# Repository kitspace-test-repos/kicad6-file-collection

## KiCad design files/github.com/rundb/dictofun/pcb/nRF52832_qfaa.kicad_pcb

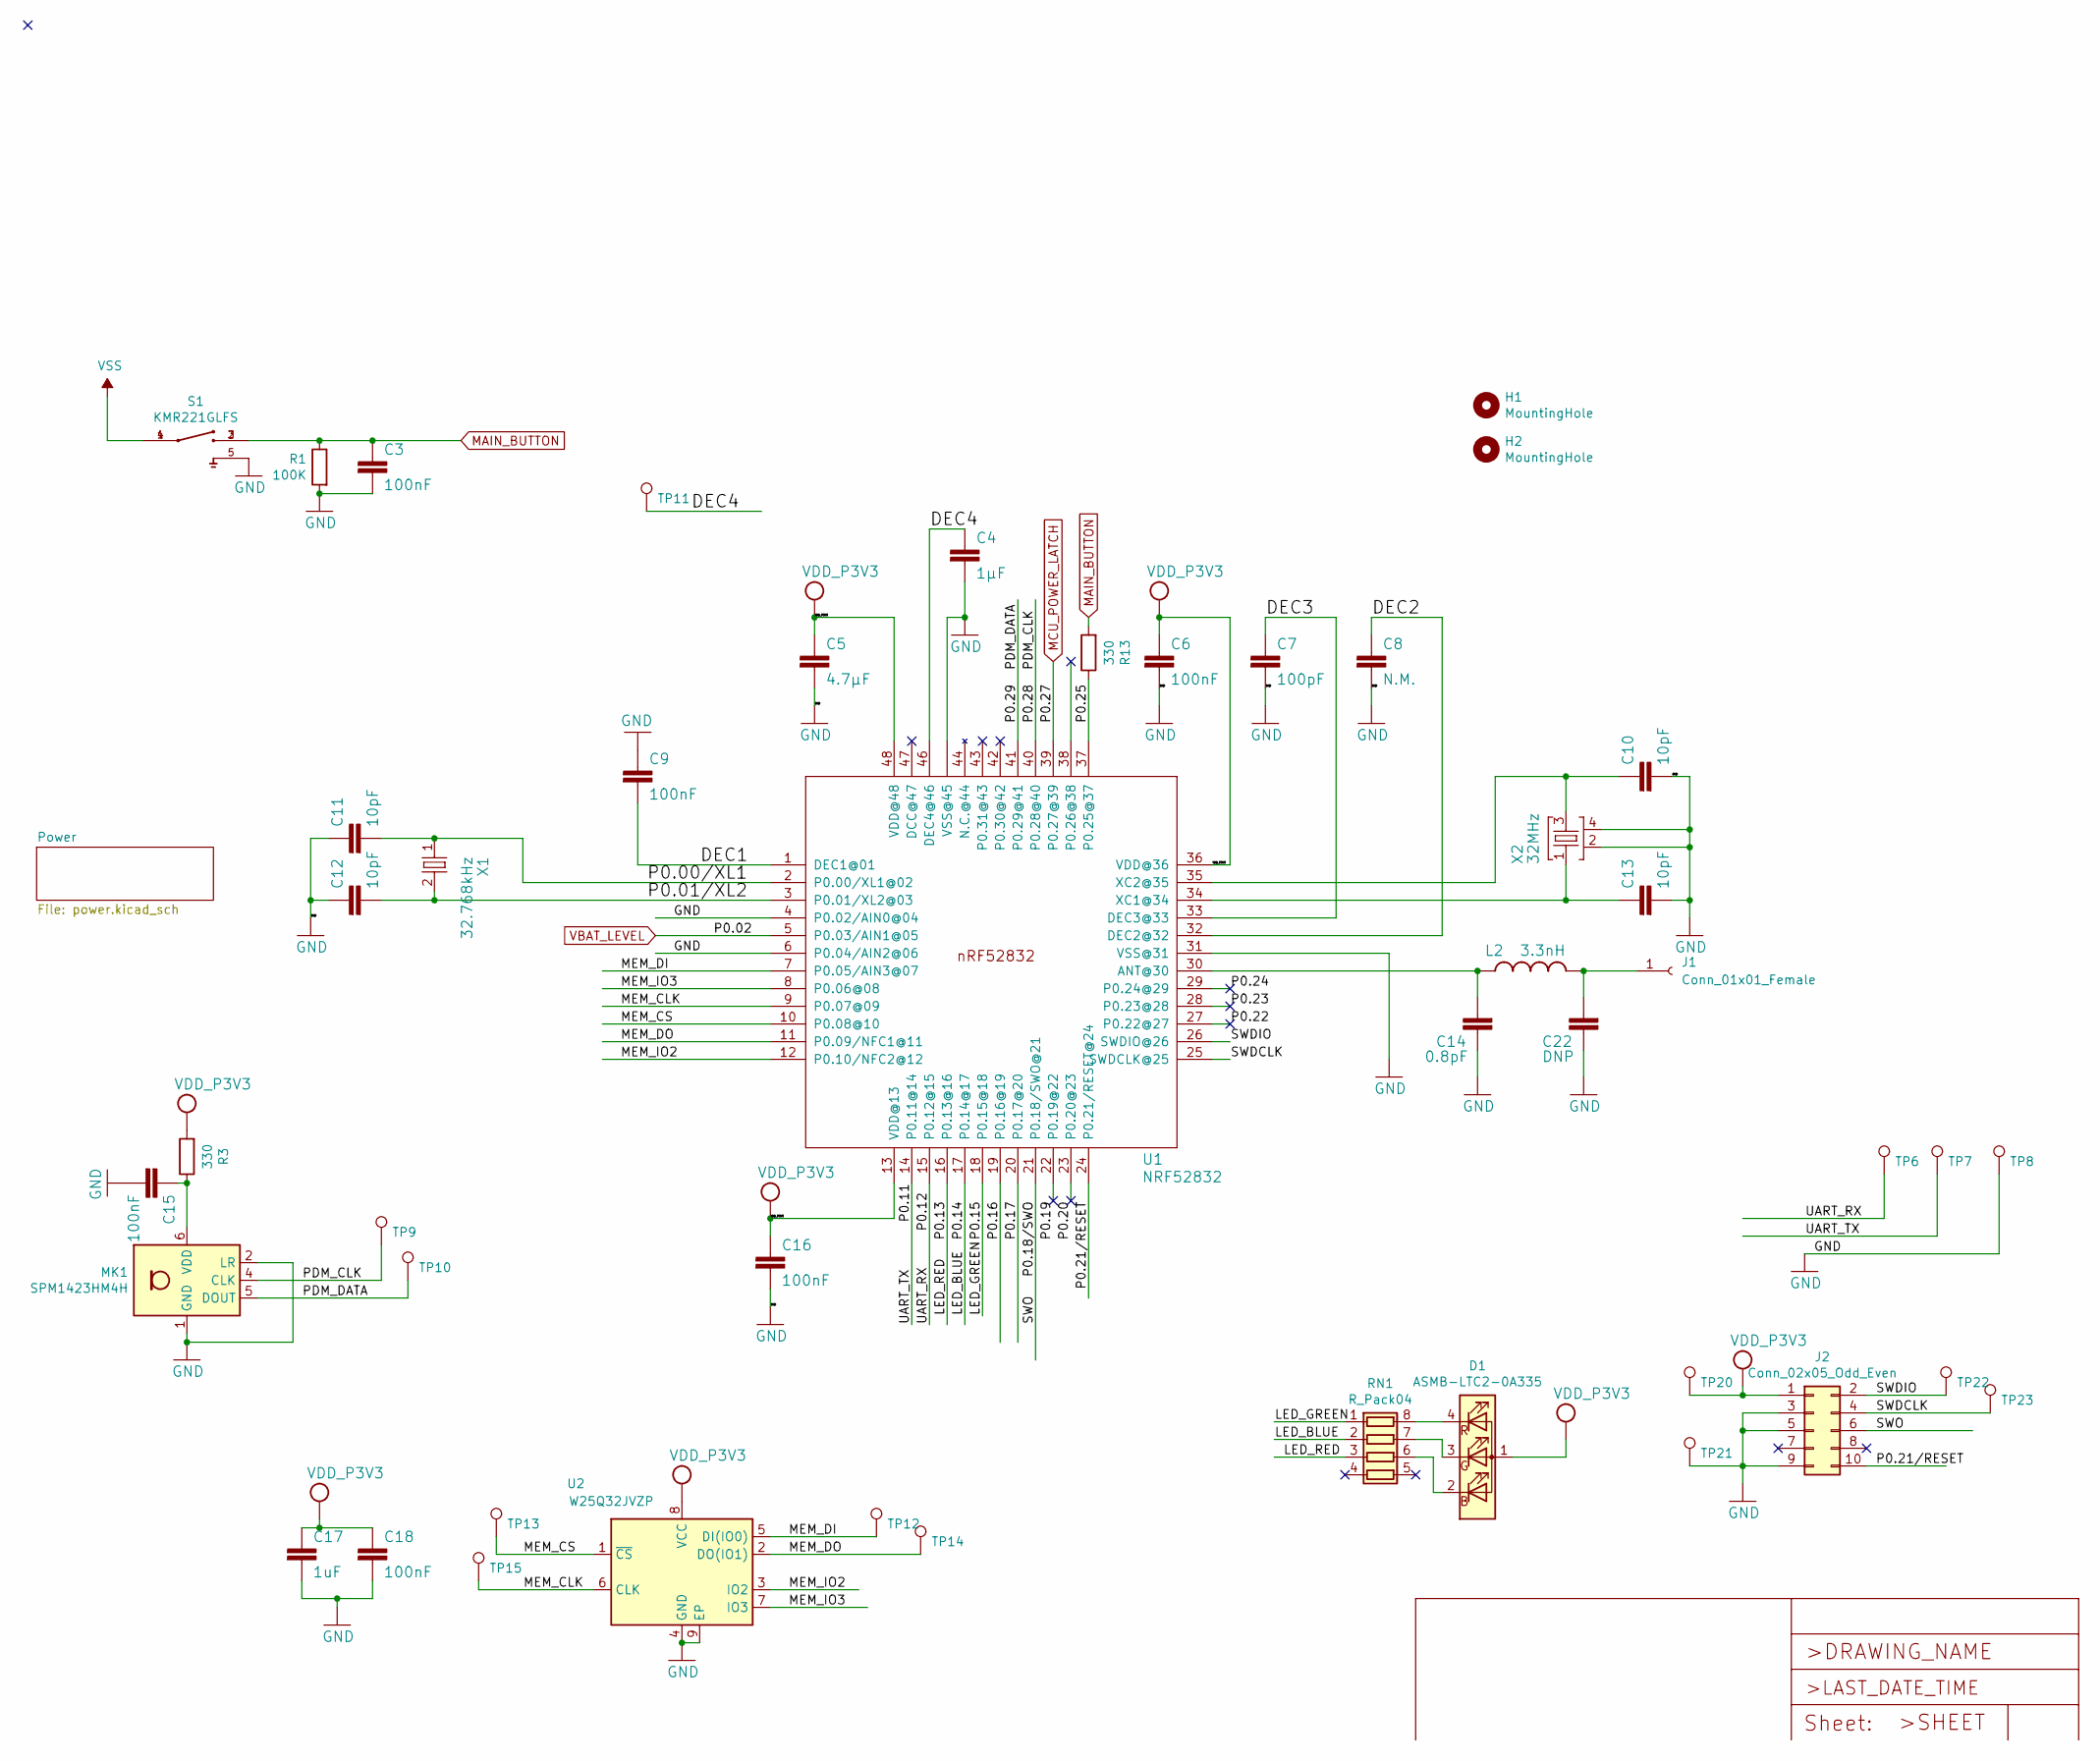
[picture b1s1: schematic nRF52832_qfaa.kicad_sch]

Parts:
C3, C6, C9, C15, C16, C18: 100nF; C_0402_1005Metric; LCSC C1525
C4: 1µF; C_0402_1005Metric; LCSC C92755
C5: 4.7µF; C_0402_1005Metric; LCSC C77004
C7: 100pF; C_0402_1005Metric; LCSC C1546
C8: N.M.; C_0402_1005Metric
C10, C11, C12, C13: 10pF; C_0402_1005Metric; LCSC C32949
C14: 0.8pF; C_0402_1005Metric; LCSC C326068
C17: 1uF; C_0402_1005Metric; LCSC C52923
C22: DNP; C_0402_1005Metric; LCSC C88902
D1: ASMB-LTC2-0A335; LED_Cree-PLCC4_2x2mm_CW
H1, H2: MountingHole; MountingHole_1mm
J1: Conn_01x01_Female; PinHeader_1x01_P1.00mm_Vertical
J2: Conn_02x05_Odd_Even; PinHeader_2x05_P1.27mm_Vertical_SMD
L2: 3.3nH; C_0402_1005Metric; LCSC C162542
MK1: SPM1423HM4H; ST_HLGA-6_3.76x4.72mm_P1.65mm
R1: 100K; R_0402_1005Metric; LCSC C25741
R3, R13: 330; R_0402_1005Metric; LCSC C25104
RN1: R_Pack04; R_Array_Convex_4x0402; LCSC C25726
S1: KMR221GLFS; SW_KMR221GLFS; LCSC C72443
TP6, TP7, TP8, TP9, TP10, TP11, TP12, TP13, TP14, TP15, TP20, TP21, TP22, TP23: TestPoint; TestPoint_Pad_D1.0mm
U1: NRF52832; QFN40P600X600X90-48_N; LCSC C77540
U2: W25Q32JVZP; WSON-8-1EP_6x5mm_P1.27mm_EP3.4x4.3mm; LCSC C2689660
X1: 32.768kHz; XTAL_3215_N
X2: 32MHz; BT-XTAL_2016_N

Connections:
/DEC1: C9.2, U1.1 (DEC1@01)
/DEC2: C8.1, U1.32 (DEC2@32)
/DEC3: C7.1, U1.33 (DEC3@33)
/DEC4: C4.1, TP11.1, U1.46 (DEC4@46)
/LED_BLUE: RN1.2 (R2.1), U1.17 (P0.14@17)
/LED_GREEN: RN1.1 (R1.1), U1.18 (P0.15@18)
/LED_RED: RN1.3 (R3.1), U1.16 (P0.13@16)
/MEM_CLK: TP15.1, U1.9 (P0.07@09), U2.6 (CLK)
/MEM_CS: TP13.1, U1.10 (P0.08@10), U2.1 (~CS)
/MEM_DI: TP12.1, U1.7 (P0.05/AIN3@07), U2.5 (DI(IO0))
/MEM_DO: TP14.1, U1.11 (P0.09/NFC1@11), U2.2 (DO(IO1))
/MEM_IO2: U1.12 (P0.10/NFC2@12), U2.3 (IO2)
/MEM_IO3: U1.8 (P0.06@08), U2.7 (IO3)
/P0.00/XL1: C11.2, U1.2 (P0.00/XL1@02), X1.1
/P0.01/XL2: C12.2, U1.3 (P0.01/XL2@03), X1.2
/P0.11: TP7.1, U1.14 (P0.11@14)
/P0.12: TP6.1, U1.15 (P0.12@15)
/P0.16: U1.19 (P0.16@19)
/P0.17: U1.20 (P0.17@20)
/P0.18/SWO: J2.6, U1.21 (P0.18/SWO@21)
/P0.19: U1.22 (P0.19@22)
/P0.20: U1.23 (P0.20@23)
/P0.21/RESET: J2.10, U1.24 (P0.21/RESET@24)
/P0.22: U1.27 (P0.22@27)
/P0.23: U1.28 (P0.23@28)
/P0.24: U1.29 (P0.24@29)
/P0.25: R13.1, U1.37 (P0.25@37)
/P0.28: MK1.4 (CLK), TP9.1, U1.40 (P0.28@40)
/P0.29: MK1.5 (DOUT), TP10.1, U1.41 (P0.29@41)
/SWDCLK: J2.4, TP23.1, U1.25 (SWDCLK@25)
/SWDIO: J2.2, TP22.1, U1.26 (SWDIO@26)
GND: C3.2, C4.2, C5.2, C6.2, C7.2, C8.2, C9.1, C10.2, C11.1, C12.1, C13.2, C14.1, C15.2, C16.2, C17.2, C18.2, C22.1, J2.3, J2.5, J2.9, MK1.1 (GND), MK1.2 (LR), MK1.3 (GND), R1.2, S1.5, TP8.1, TP21.1, U1.4 (P0.02/AIN0@04), U1.6 (P0.04/AIN2@06), U1.31 (VSS@31), U1.45 (VSS@45), U1.PAD (VSS@45), U1.PAD@VIA01 (VSS@45), U1.PAD@VIA02 (VSS@45), U1.PAD@VIA03 (VSS@45), U1.PAD@VIA04 (VSS@45), U1.PAD@VIA05 (VSS@45), U1.PAD@VIA06 (VSS@45), U1.PAD@VIA07 (VSS@45), U1.PAD@VIA08 (VSS@45), U1.PAD@VIA09 (VSS@45), U1.PAD@VIA10 (VSS@45), U1.PAD@VIA11 (VSS@45), U1.PAD@VIA12 (VSS@45), U1.PAD@VIA13 (VSS@45), U1.PAD@VIA14 (VSS@45), U1.PAD@VIA15 (VSS@45), U1.PAD@VIA16 (VSS@45), U2.4 (GND), U2.9 (EP), X2.2, X2.4; also elsewhere on the board
MAIN_BUTTON: C3.1, R1.1, R13.2, S1.2, S1.3; also elsewhere on the board
MCU_POWER_LATCH: U1.39 (P0.27@39); also elsewhere on the board
unnamed: C10.1, U1.35 (XC2@35), X2.3
unnamed: C13.1, U1.34 (XC1@34), X2.1
unnamed: C14.2, L2.1, U1.30 (ANT@30)
unnamed: C15.1, MK1.6 (VDD), R3.1
unnamed: C22.2, J1.1, L2.2
unnamed: D1.2 (BK), RN1.6 (R3.2)
unnamed: D1.3 (GK), RN1.7 (R2.2)
unnamed: D1.4 (RK), RN1.8 (R1.2)
VBAT_LEVEL: U1.5 (P0.03/AIN1@05); also elsewhere on the board
VCC: C5.1, C6.1, C16.1, C17.1, C18.1, D1.1 (A), J2.1, R3.2, TP20.1, U1.13 (VDD@13), U1.36 (VDD@36), U1.48 (VDD@48), U2.8 (VCC); also elsewhere on the board
VSS: S1.1, S1.4; also elsewhere on the board

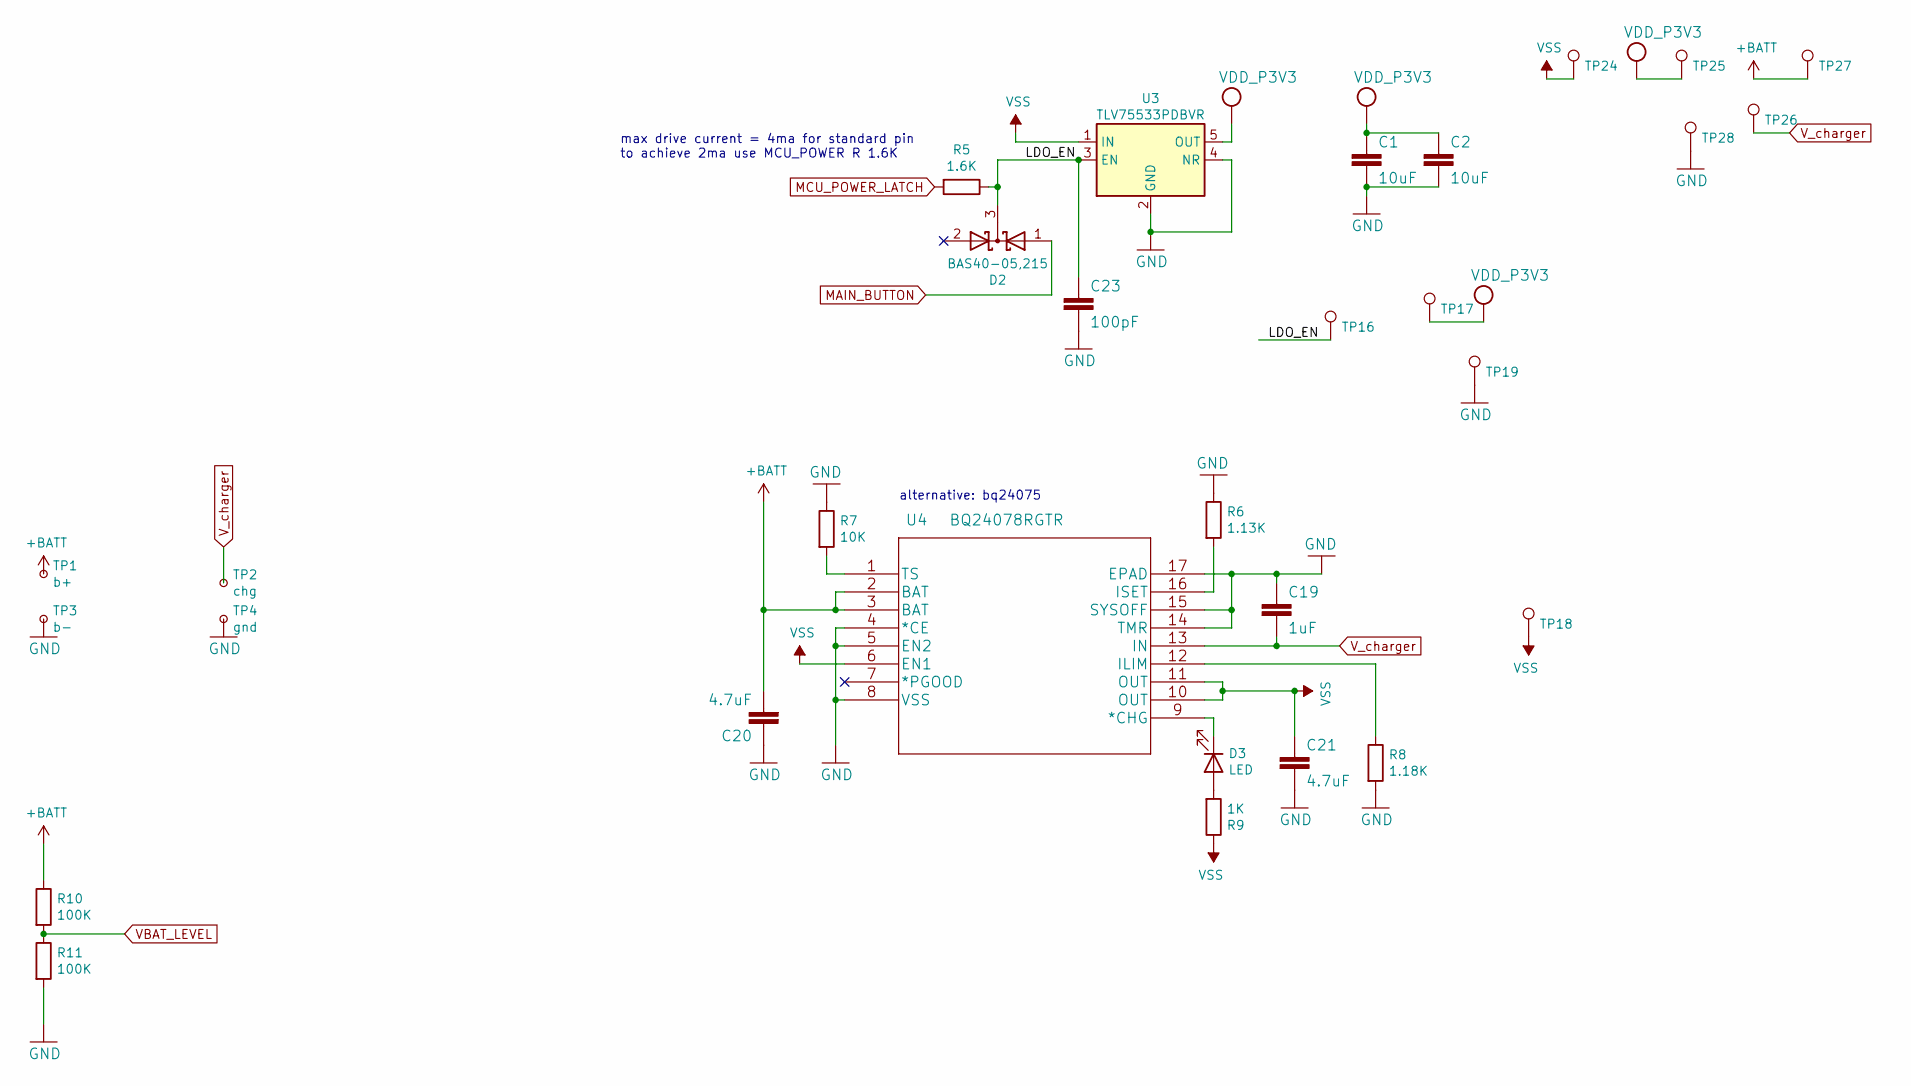
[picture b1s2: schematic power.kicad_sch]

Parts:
C1, C2: 10uF; C_0402_1005Metric; LCSC C15525
C19: 1uF; C_0402_1005Metric; LCSC C52923
C20, C21: 4.7uF; C_0402_1005Metric; LCSC C23733
C23: 100pF; C_0402_1005Metric; LCSC C1546
D2: BAS40-05,215; SOT-23; LCSC C85391
D3: LED; LED_0603_1608Metric; LCSC C72043
R5: 1.6K; R_0402_1005Metric; LCSC C25867
R6: 1.13K; R_0402_1005Metric; LCSC C67014
R7: 10K; R_0402_1005Metric; LCSC C25744
R8: 1.18K; R_0402_1005Metric; LCSC C270651
R9: 1K; R_0402_1005Metric; LCSC C11702
R10, R11: 100K; R_0402_1005Metric; LCSC C25741
TP1: b+; TestPoint_Pad_D1.0mm
TP2: chg; TestPoint_Pad_D1.0mm
TP3: b-; TestPoint_Pad_D1.0mm
TP4: gnd; TestPoint_Pad_D1.0mm
TP16, TP17, TP18, TP19, TP24, TP25, TP26, TP27, TP28: TestPoint; TestPoint_Pad_D1.0mm
U3: TLV75533PDBVR; SOT-23-5; LCSC C404027
U4: BQ24078RGTR; VQFN-16-1EP_3x3mm_P0.5mm_EP1.45x1.45mm_ThermalVias; LCSC C15464

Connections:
+BATT: C20.2, R10.1, TP1.1, TP27.1, U4.2 (BAT), U4.3 (BAT)
/Power/LDO_EN: C23.1, D2.3 (K), R5.1, TP16.1, U3.3 (EN)
GND: C1.2, C2.2, C19.1, C20.1, C21.2, C23.2, R6.1, R7.1, R8.2, R11.2, TP3.1, TP4.1, TP19.1, TP28.1, U3.2 (GND), U3.4 (NR), U4.4 (*CE), U4.5 (EN2), U4.8 (VSS), U4.14 (TMR), U4.15 (SYSOFF), U4.17 (EPAD); also elsewhere on the board
MAIN_BUTTON: D2.1 (A); also elsewhere on the board
MCU_POWER_LATCH: R5.2; also elsewhere on the board
unnamed: D3.1 (K), U4.9 (*CHG)
unnamed: D3.2 (A), R9.2
unnamed: R6.2, U4.16 (ISET)
unnamed: R7.2, U4.1 (TS)
unnamed: R8.1, U4.12 (ILIM)
VBAT_LEVEL: R10.2, R11.1; also elsewhere on the board
VCC: C1.1, C2.1, TP17.1, TP25.1, U3.5 (OUT); also elsewhere on the board
VSS: C21.1, R9.1, TP18.1, TP24.1, U3.1 (IN), U4.6 (EN1), U4.10 (OUT), U4.11 (OUT); also elsewhere on the board
V_charger: C19.2, TP2.1, TP26.1, U4.13 (IN)

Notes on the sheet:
alternative: bq24075
max drive current = 4ma for standard pin to achieve 2ma use MCU_POWER R 1.6K

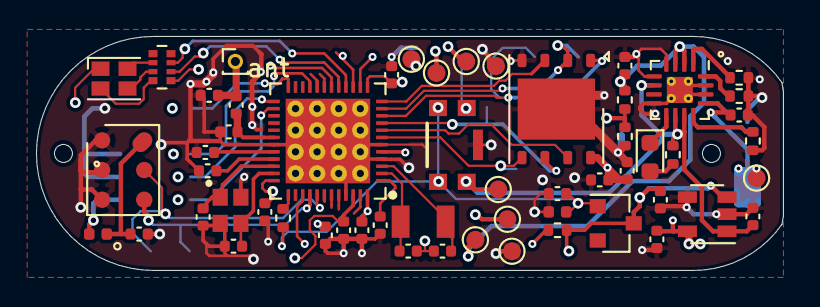
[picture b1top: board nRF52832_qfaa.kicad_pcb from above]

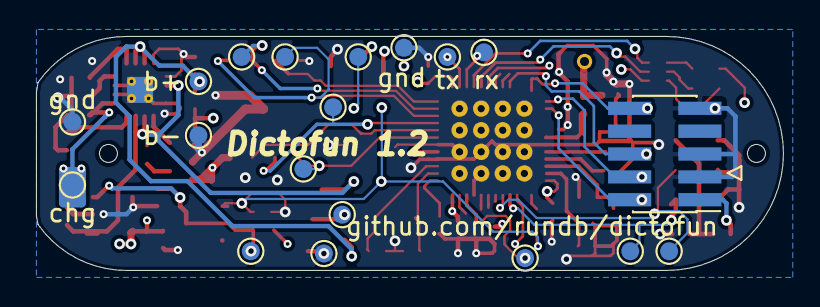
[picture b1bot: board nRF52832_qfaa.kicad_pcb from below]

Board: 4 copper layers, 41.5 x 13.0 mm, 77 parts (19 on the bottom side), 46 nets.

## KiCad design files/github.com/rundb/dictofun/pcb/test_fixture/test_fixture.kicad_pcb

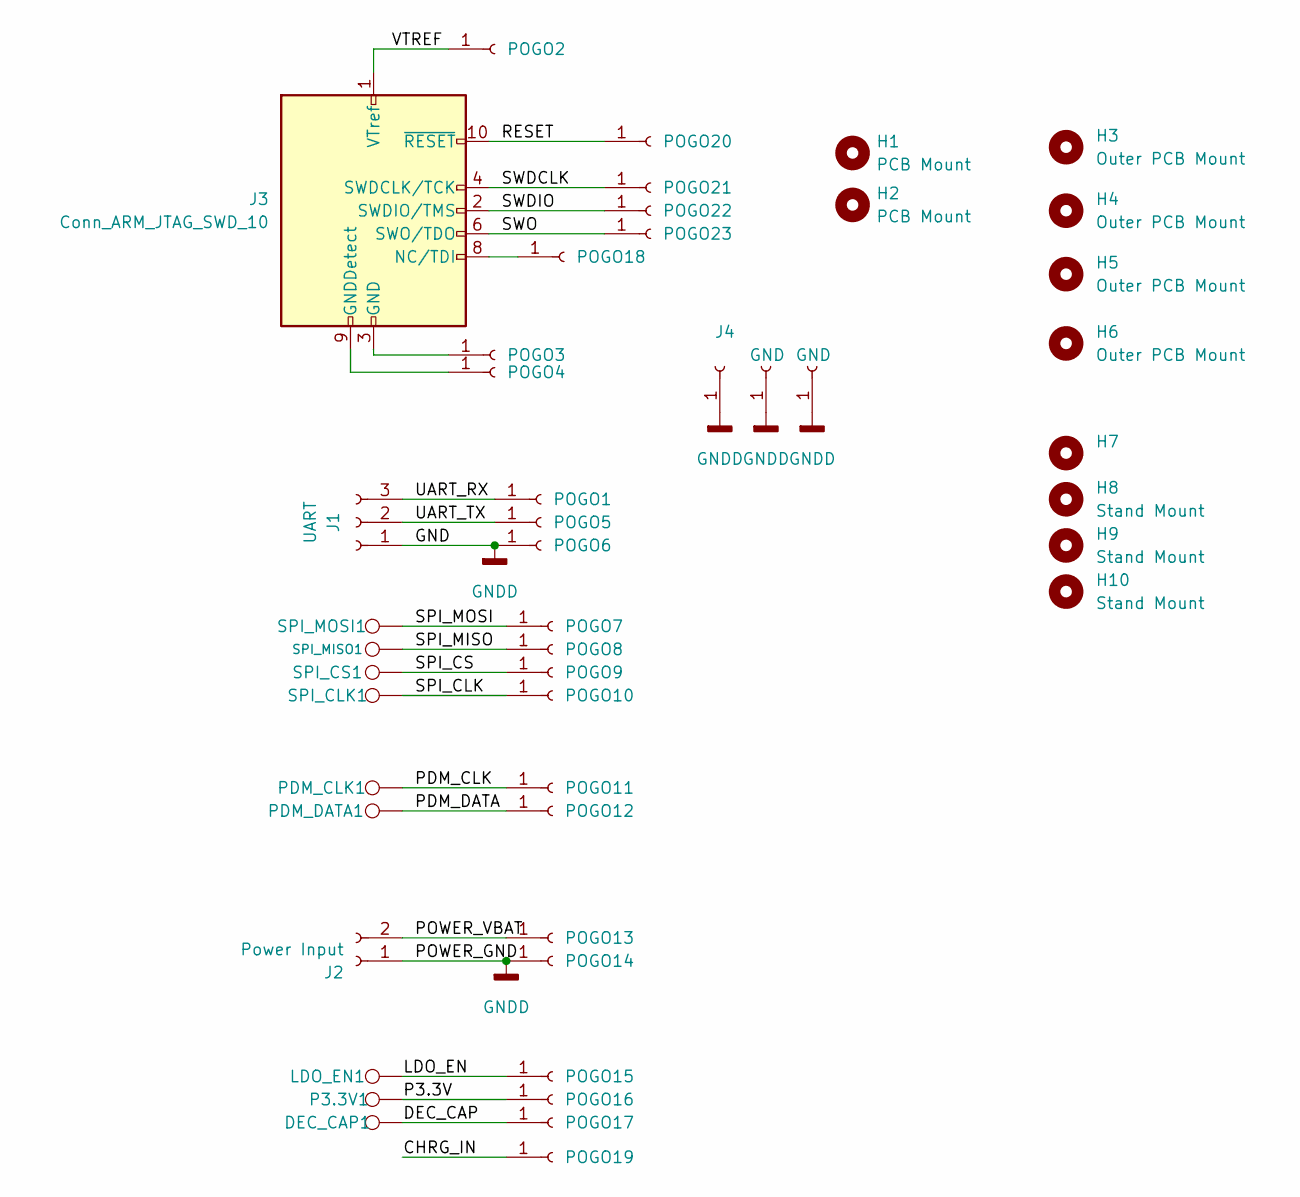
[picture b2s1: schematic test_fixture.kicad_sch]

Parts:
DEC_CAP1: TestPoint_Pad_D1.5mm
H1, H2: PCB Mount; MountingHole_2.1mm
H3, H4, H5, H6: Outer PCB Mount; MountingHole_2.1mm
H7: (no value)
H8, H9, H10: Stand Mount; MountingHole_2.1mm
J1: UART; PinHeader_1x03_P2.54mm_Vertical
J2: Power Input; PinHeader_1x02_P2.54mm_Vertical
J3: Conn_ARM_JTAG_SWD_10; PinHeader_2x05_P1.27mm_Vertical_SMD
J4: PinSocket_1x01_P2.54mm_Vertical
J5, J6: GND; PinSocket_1x01_P2.54mm_Vertical
LDO_EN1: TestPoint_Pad_D1.5mm
P3.3V1: TestPoint_Pad_D1.5mm
PDM_CLK1: TestPoint_Pad_D1.5mm
PDM_DATA1: TestPoint_Pad_D1.5mm
POGO1, POGO2, POGO3, POGO4, POGO5, POGO6, POGO7, POGO8, POGO9, POGO10, POGO11, POGO12, POGO13, POGO14, POGO15, POGO16, POGO17, POGO18, POGO19, POGO20, POGO21, POGO22, POGO23: pogo; POGO_PIN
SPI_CLK1: TestPoint_Pad_D1.5mm
SPI_CS1: TestPoint_Pad_D1.5mm
SPI_MISO1: TestPoint_Pad_D1.5mm
SPI_MOSI1: TestPoint_Pad_D1.5mm

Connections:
/CHRG_IN: POGO19.1
/DEC_CAP: DEC_CAP1.1, POGO17.1
/LDO_EN: LDO_EN1.1, POGO15.1
/P3.3V: P3.3V1.1, POGO16.1
/PDM_CLK: PDM_CLK1.1, POGO11.1
/PDM_DATA: PDM_DATA1.1, POGO12.1
/POWER_VBAT: J2.2, POGO13.1
/RESET: J3.10 (~RESET), POGO20.1
/SPI_CLK: POGO10.1, SPI_CLK1.1
/SPI_CS: POGO9.1, SPI_CS1.1
/SPI_MISO: POGO8.1, SPI_MISO1.1
/SPI_MOSI: POGO7.1, SPI_MOSI1.1
/SWDCLK: J3.4 (SWDCLK/TCK), POGO21.1
/SWDIO: J3.2 (SWDIO/TMS), POGO22.1
/SWO: J3.6 (SWO/TDO), POGO23.1
/UART_RX: J1.3, POGO1.1
/UART_TX: J1.2, POGO5.1
/VTREF: J3.1 (VTref), POGO2.1
GNDD: J1.1, J2.1, J4.1, J5.1, J6.1, POGO6.1, POGO14.1
unnamed: J3.3 (GND), J3.5 (GND), POGO3.1
unnamed: J3.8 (NC/TDI), POGO18.1
unnamed: J3.9 (GNDDetect), POGO4.1

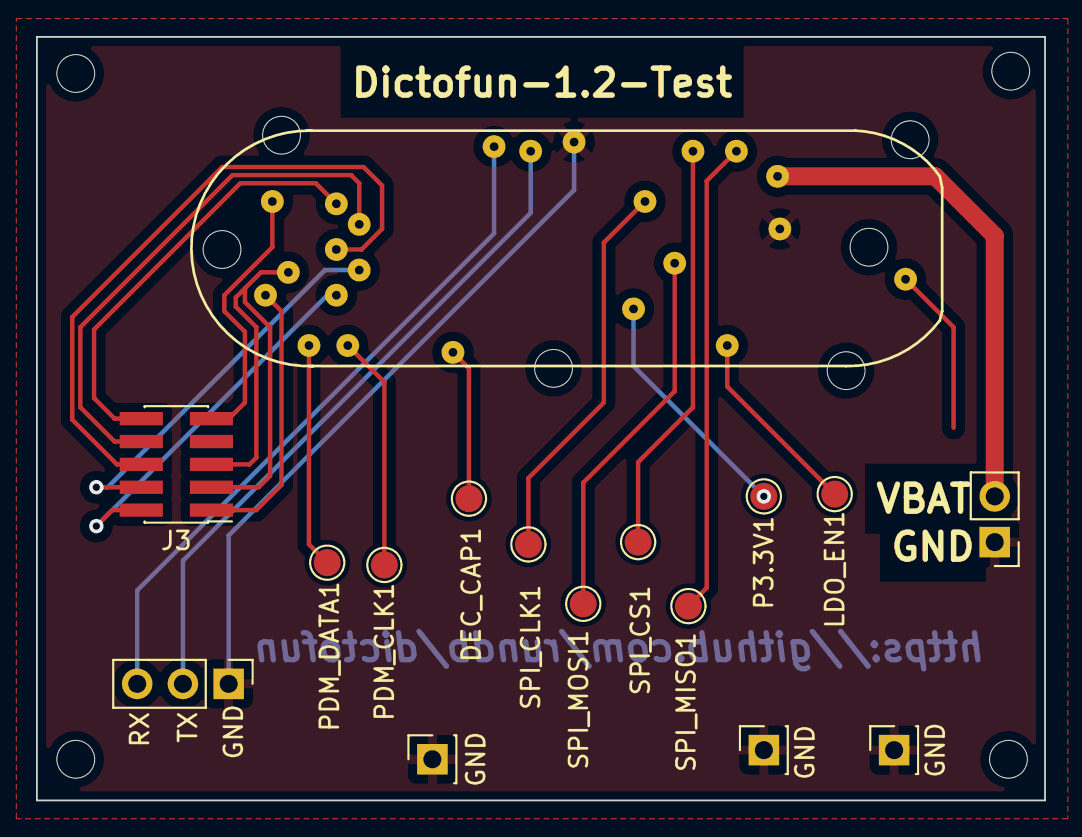
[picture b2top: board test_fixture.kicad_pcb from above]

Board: 2 copper layers, 56.0 x 42.4 mm, 48 parts (0 on the bottom side), 21 nets.

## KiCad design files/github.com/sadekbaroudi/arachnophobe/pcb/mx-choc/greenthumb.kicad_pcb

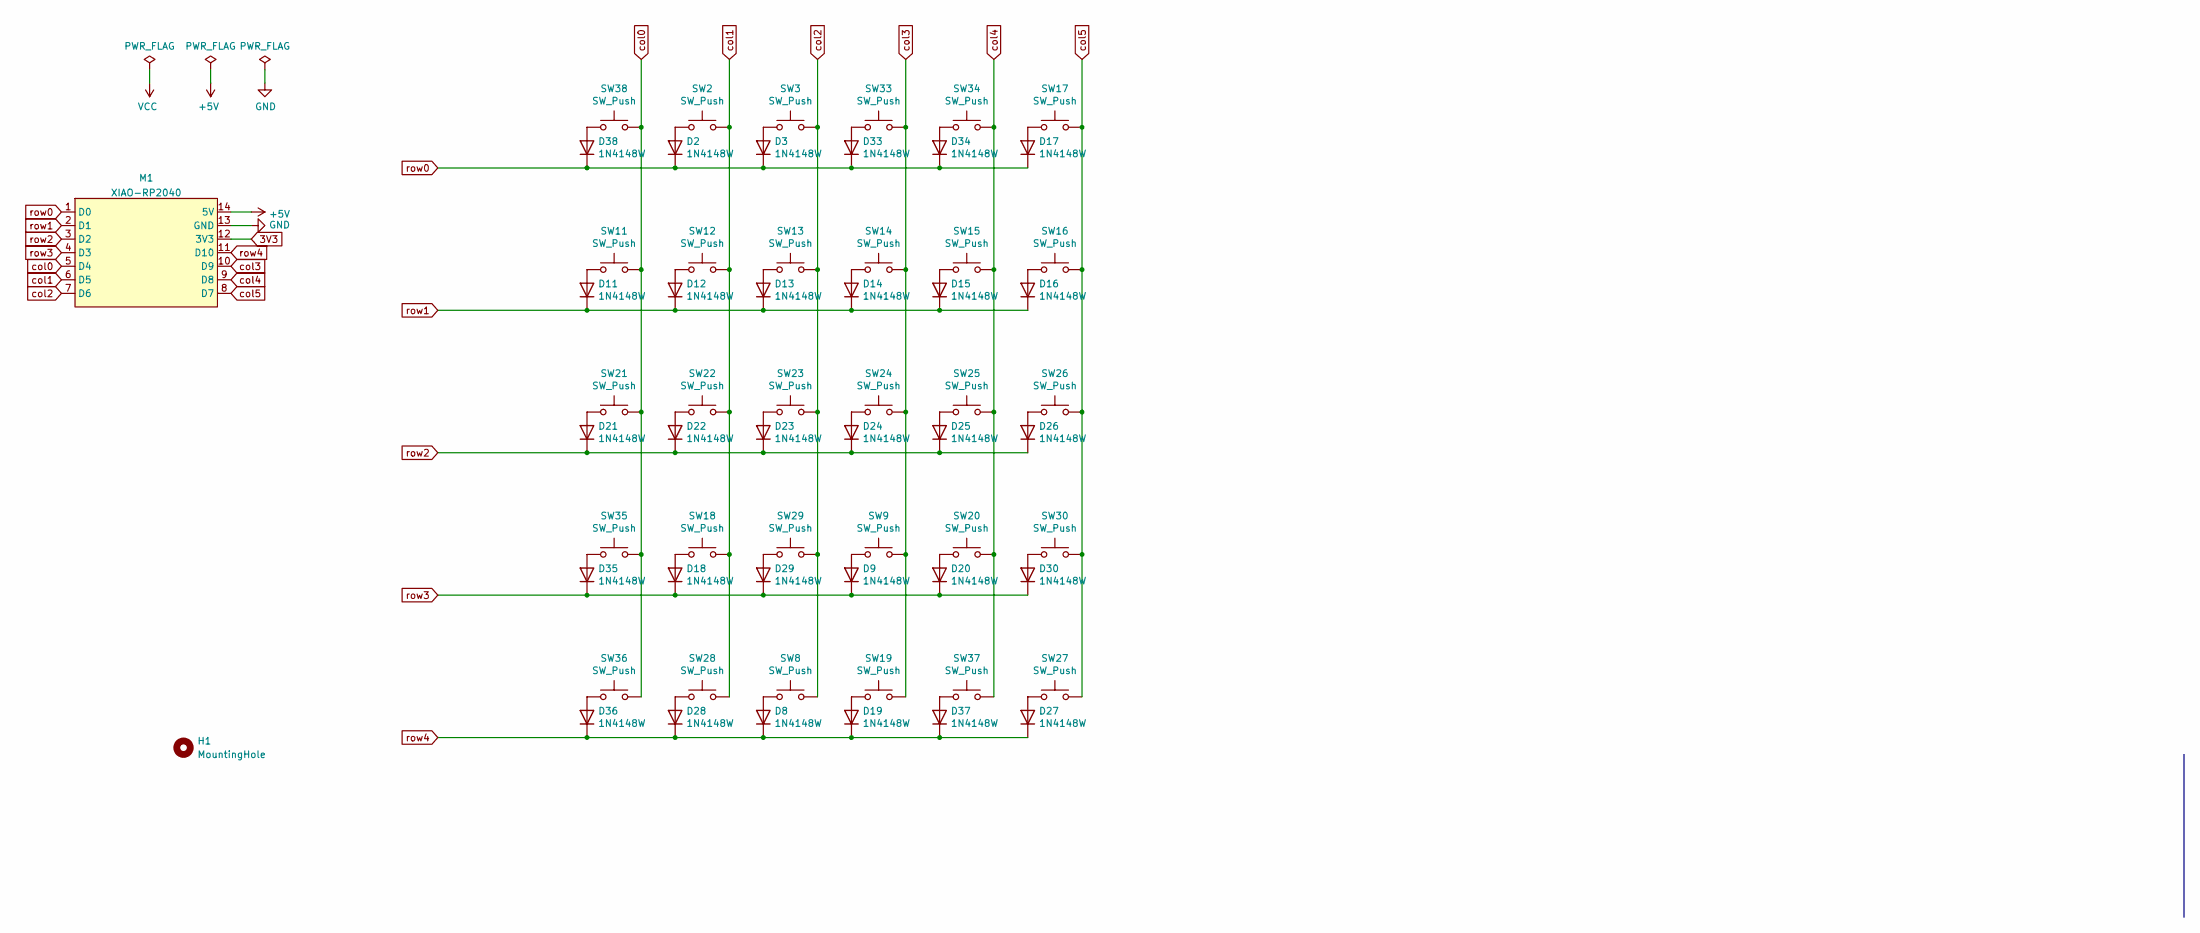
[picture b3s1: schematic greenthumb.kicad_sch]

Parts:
D2, D3, D8, D9, D11, D12, D13, D14, D15, D16, D17, D18, D19, D20, D21, D22, D23, D24, D25, D26, D27, D28, D29, D30, D33, D34, D35, D36, D37, D38: 1N4148W; D_SOD-123; LCSC C909967
H1: MountingHole; fingerpunch-logo
M1: XIAO-RP2040; LCSC 102010428
SW2, SW3, SW8, SW9, SW11, SW12, SW13, SW14, SW15, SW16, SW17, SW18, SW19, SW20, SW21, SW22, SW23, SW24, SW25, SW26, SW27, SW28, SW29, SW30, SW33, SW34, SW35, SW36, SW37, SW38: SW_Push; Kailh_socket_MX-ChocV1

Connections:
3V3: M1.12 (3V3)
+5V: M1.14 (5V)
GND: M1.13 (GND)
unnamed: D2.2 (A), SW2.1
unnamed: D3.2 (A), SW3.1
unnamed: D8.2 (A), SW8.1
unnamed: D9.2 (A), SW9.1
unnamed: D11.2 (A), SW11.1
unnamed: D12.2 (A), SW12.1
unnamed: D13.2 (A), SW13.1
unnamed: D14.2 (A), SW14.1
unnamed: D15.2 (A), SW15.1
unnamed: D16.2 (A), SW16.1
unnamed: D17.2 (A), SW17.1
unnamed: D18.2 (A), SW18.1
unnamed: D19.2 (A), SW19.1
unnamed: D20.2 (A), SW20.1
unnamed: D21.2 (A), SW21.1
unnamed: D22.2 (A), SW22.1
unnamed: D23.2 (A), SW23.1
unnamed: D24.2 (A), SW24.1
unnamed: D25.2 (A), SW25.1
unnamed: D26.2 (A), SW26.1
unnamed: D27.2 (A), SW27.1
unnamed: D28.2 (A), SW28.1
unnamed: D29.2 (A), SW29.1
unnamed: D30.2 (A), SW30.1
unnamed: D33.2 (A), SW33.1
unnamed: D34.2 (A), SW34.1
unnamed: D35.2 (A), SW35.1
unnamed: D36.2 (A), SW36.1
unnamed: D37.2 (A), SW37.1
unnamed: D38.2 (A), SW38.1
col0: M1.5 (D4), SW11.2, SW21.2, SW35.2, SW36.2, SW38.2
col1: M1.6 (D5), SW2.2, SW12.2, SW18.2, SW22.2, SW28.2
col2: M1.7 (D6), SW3.2, SW8.2, SW13.2, SW23.2, SW29.2
col3: M1.10 (D9), SW9.2, SW14.2, SW19.2, SW24.2, SW33.2
col4: M1.9 (D8), SW15.2, SW20.2, SW25.2, SW34.2, SW37.2
col5: M1.8 (D7), SW16.2, SW17.2, SW26.2, SW27.2, SW30.2
row0: D2.1 (K), D3.1 (K), D17.1 (K), D33.1 (K), D34.1 (K), D38.1 (K), M1.1 (D0)
row1: D11.1 (K), D12.1 (K), D13.1 (K), D14.1 (K), D15.1 (K), D16.1 (K), M1.2 (D1)
row2: D21.1 (K), D22.1 (K), D23.1 (K), D24.1 (K), D25.1 (K), D26.1 (K), M1.3 (D2)
row3: D9.1 (K), D18.1 (K), D20.1 (K), D29.1 (K), D30.1 (K), D35.1 (K), M1.4 (D3)
row4: D8.1 (K), D19.1 (K), D27.1 (K), D28.1 (K), D36.1 (K), D37.1 (K), M1.11 (D10)

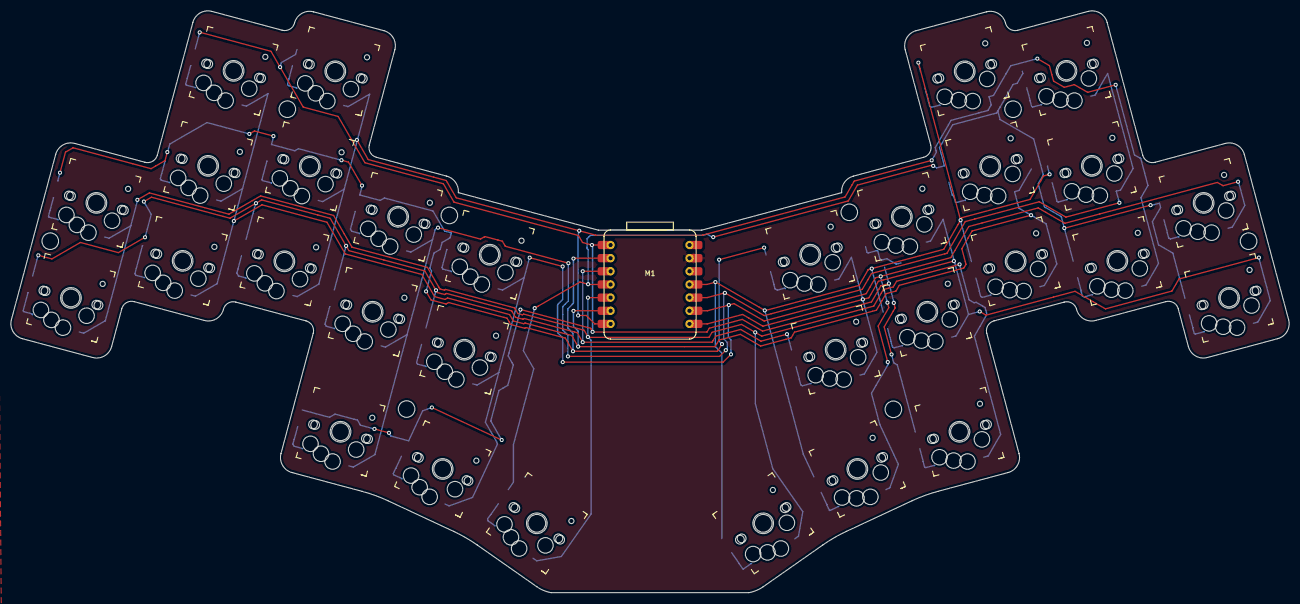
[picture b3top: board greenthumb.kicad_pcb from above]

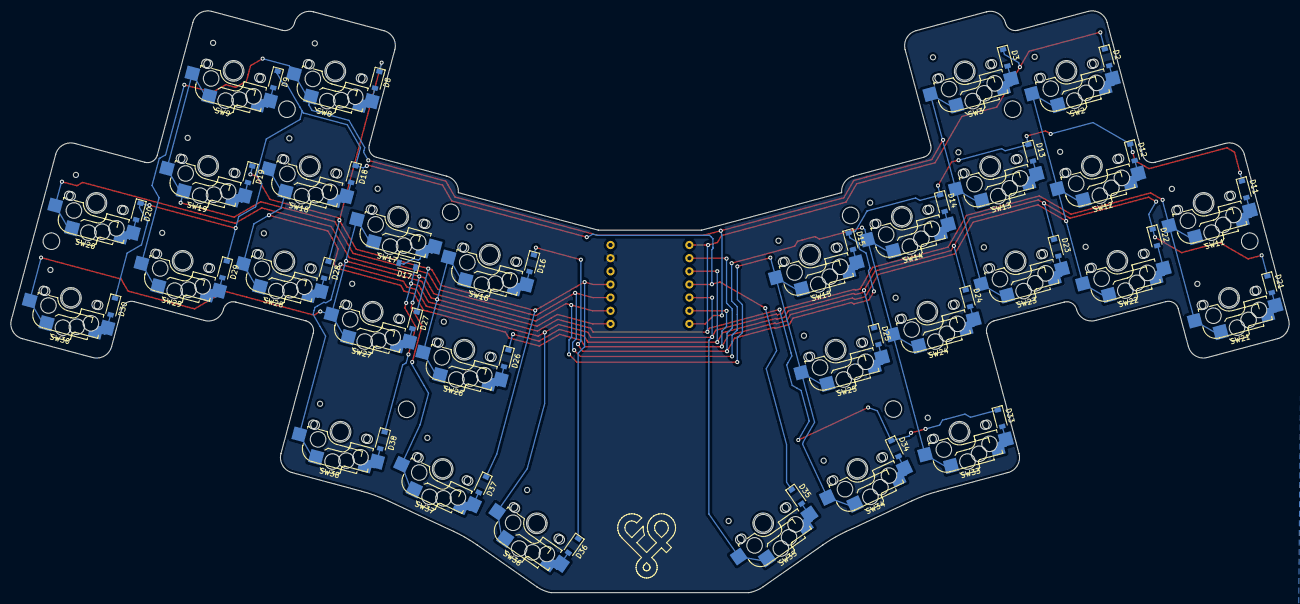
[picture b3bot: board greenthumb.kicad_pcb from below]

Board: 2 copper layers, 246.9 x 112.4 mm, 62 parts (31 on the bottom side), 41 nets.

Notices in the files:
files/github.com/skiselev/flock/KiCad/Z80-FDC.kicad_pcb:
Licensed under CERN-OHL-S: https://cern-ohl.web.cern.ch
Copyright (C) 2022 Sergey Kiselev
